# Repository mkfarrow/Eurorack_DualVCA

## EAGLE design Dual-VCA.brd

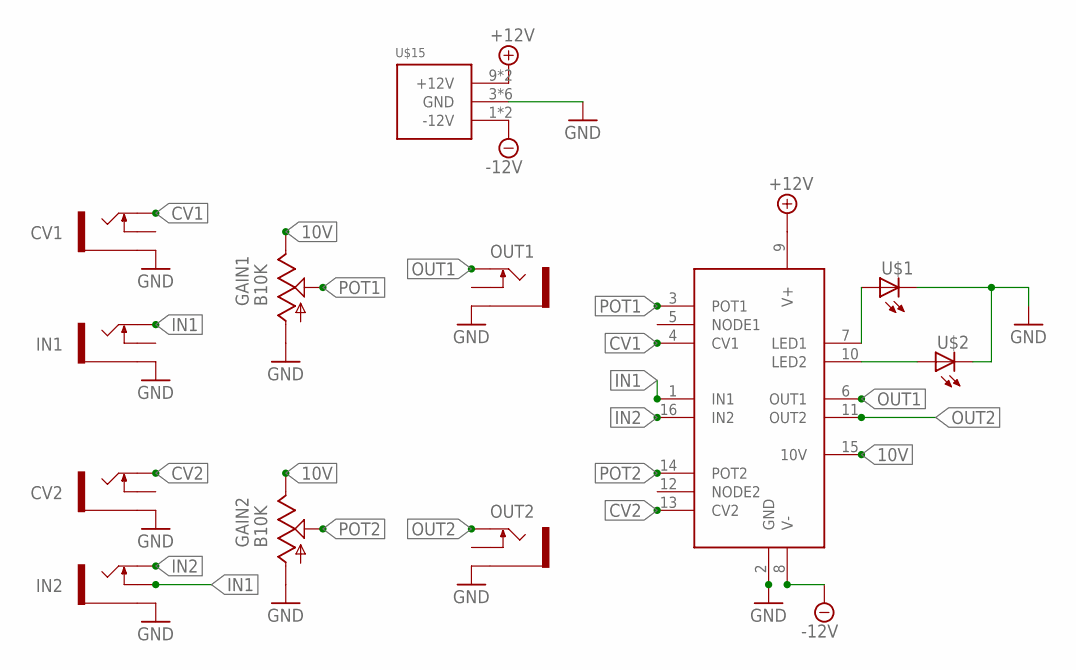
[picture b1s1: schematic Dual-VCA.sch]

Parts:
CV1, CV2: THONKICONN-SOCKETS-PJ301M-12NEW; THONKICONN-SOCKETS-PJ301M-12
GAIN1, GAIN2: B10K; MUSICTHINGMODULAR_9MM_SNAP-IN_POT
IN1, IN2: THONKICONN-SOCKETS-PJ301M-12NEW; THONKICONN-SOCKETS-PJ301M-12
OUT1, OUT2: THONKICONN-SOCKETS-PJ301M-12NEW; THONKICONN-SOCKETS-PJ301M-12
U1: ES_2164_V2
U$1, U$2: LED3MM
U$15: POWER_SIMPLE10; POWER_10

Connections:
10V: GAIN1.3 (E), GAIN2.3 (E), U1.15 (10V)
+12V: U1.9 (V+), U$15.9 (+12V), U$15.10 (+12V)
-12V: U1.8 (V-), U$15.1 (-12V), U$15.2 (-12V)
CV1: CV1.P$1_TIP (TIP), U1.4 (CV1)
CV2: CV2.P$1_TIP (TIP), U1.13 (CV2)
GND: CV1.P$3_SLEEVE (SLEEVE), CV2.P$3_SLEEVE (SLEEVE), GAIN1.1 (A), GAIN2.1 (A), IN1.P$3_SLEEVE (SLEEVE), IN2.P$3_SLEEVE (SLEEVE), OUT1.P$3_SLEEVE (SLEEVE), OUT2.P$3_SLEEVE (SLEEVE), U1.2 (GND), U$1.K (C), U$2.K (C), U$15.3 (GND), U$15.4 (GND), U$15.5 (GND), U$15.6 (GND), U$15.7 (GND), U$15.8 (GND)
IN1: IN1.P$1_TIP (TIP), IN2.P$2_SWITCH (SWITCH), U1.1 (IN1)
IN2: IN2.P$1_TIP (TIP), U1.16 (IN2)
unnamed: U1.7 (LED1), U$1.A
unnamed: U1.10 (LED2), U$2.A
OUT1: OUT1.P$1_TIP (TIP), U1.6 (OUT1)
OUT2: OUT2.P$1_TIP (TIP), U1.11 (OUT2)
POT1: GAIN1.2 (S), U1.3 (POT1)
POT2: GAIN2.2 (S), U1.14 (POT2)

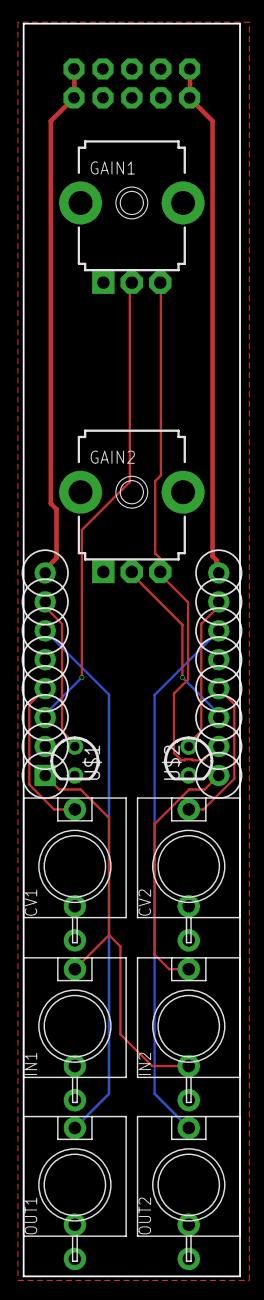
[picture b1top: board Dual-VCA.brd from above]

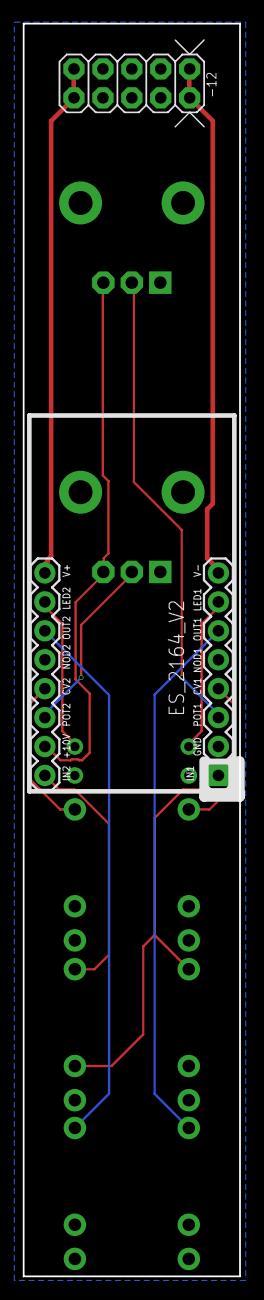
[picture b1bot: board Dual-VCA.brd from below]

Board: 2 copper layers, 19.0 x 110.0 mm, 12 parts (2 on the bottom side), 14 nets.

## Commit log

2022-12-21 adding eagle files
2022-12-22 adding images
